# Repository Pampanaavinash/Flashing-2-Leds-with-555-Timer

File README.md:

# Flashing-2-Leds-with-555-Timer

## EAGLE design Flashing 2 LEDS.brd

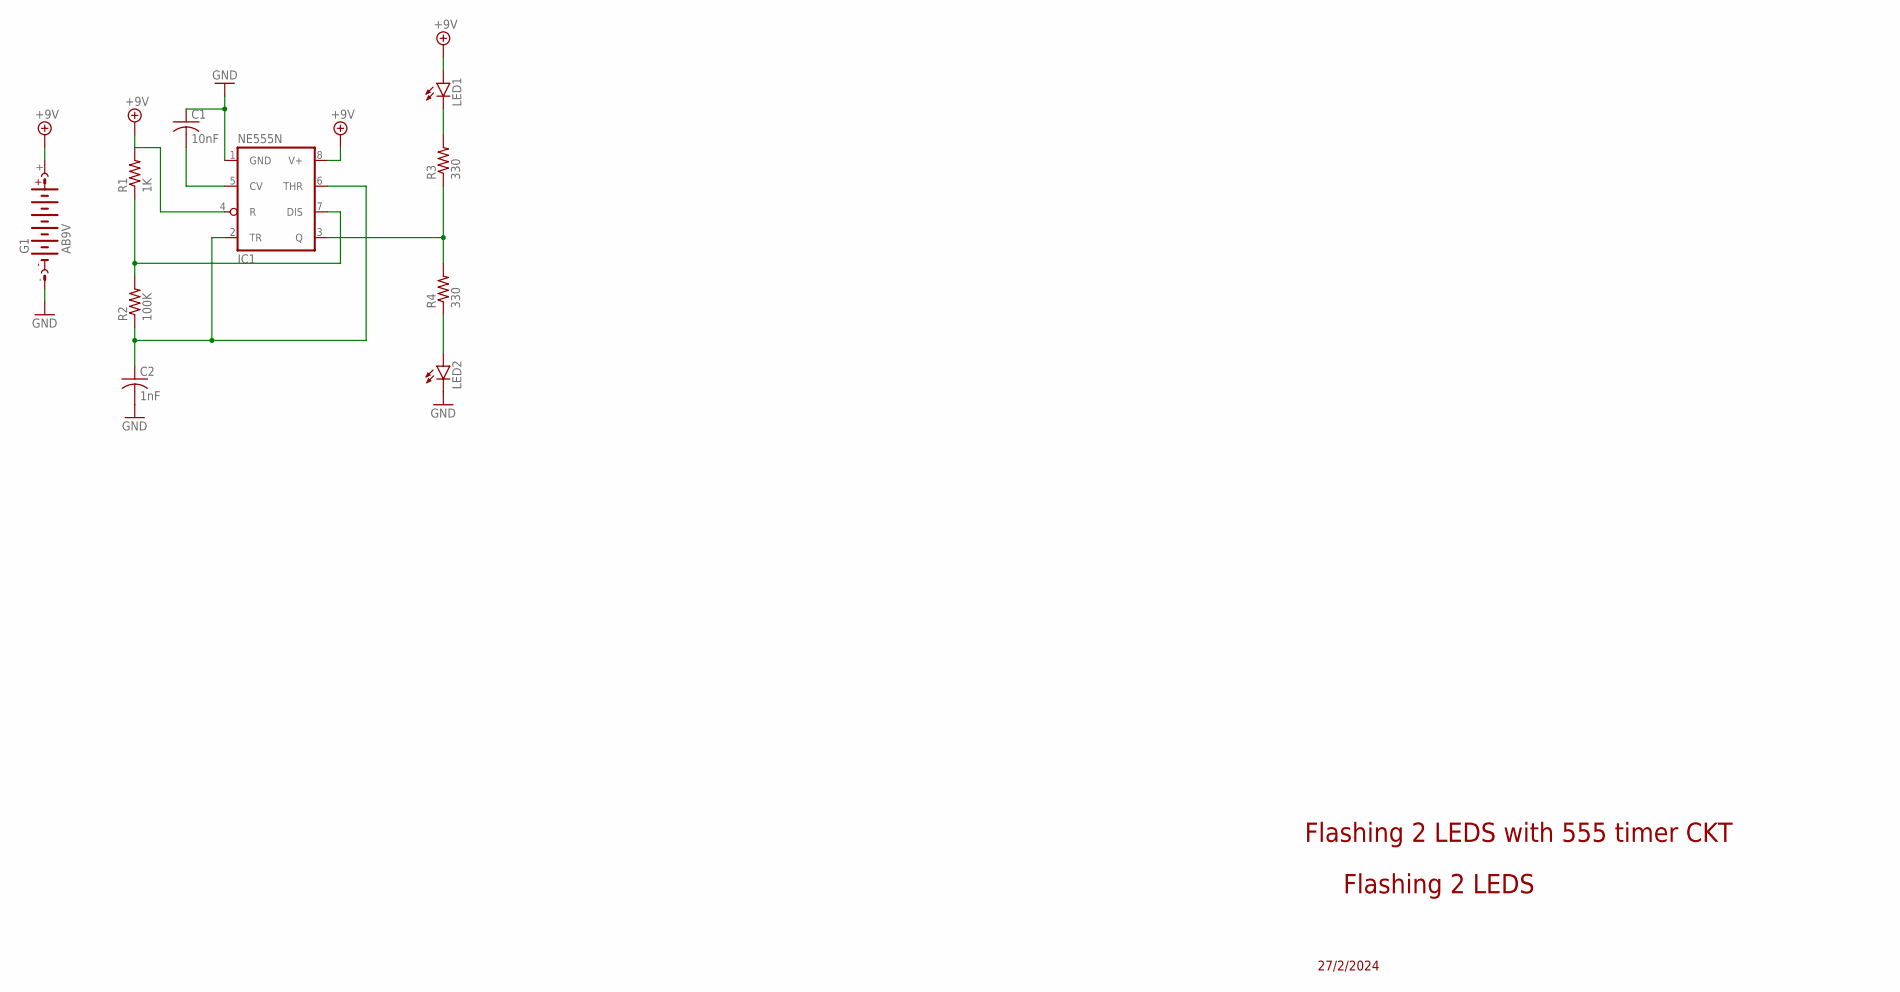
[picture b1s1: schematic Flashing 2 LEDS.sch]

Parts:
C1: 10nF; C1206
C2: 1nF; C1206
G1: AB9V
IC1: NE555N; DIL08
LED1, LED2: LED5MM
R1: 1K; R0603
R2: 100K; R0603
R3, R4: 330; R0603

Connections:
+9V: G1.+, IC1.4 (R), IC1.8 (V+), LED1.A, R1.2
GND: C1.1, C2.2, G1.-, IC1.1 (GND), LED2.K (C)
unnamed: IC1.7 (DIS), R1.1, R2.2
unnamed: C2.1, IC1.2 (TR), IC1.6 (THR), R2.1
unnamed: LED1.K (C), R3.2
unnamed: IC1.3 (Q), R3.1, R4.2
unnamed: LED2.A, R4.1
unnamed: C1.2, IC1.5 (CV)

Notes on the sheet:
Flashing 2 LEDS
27/2/2024
Flashing 2 LEDS with 555 timer CKT

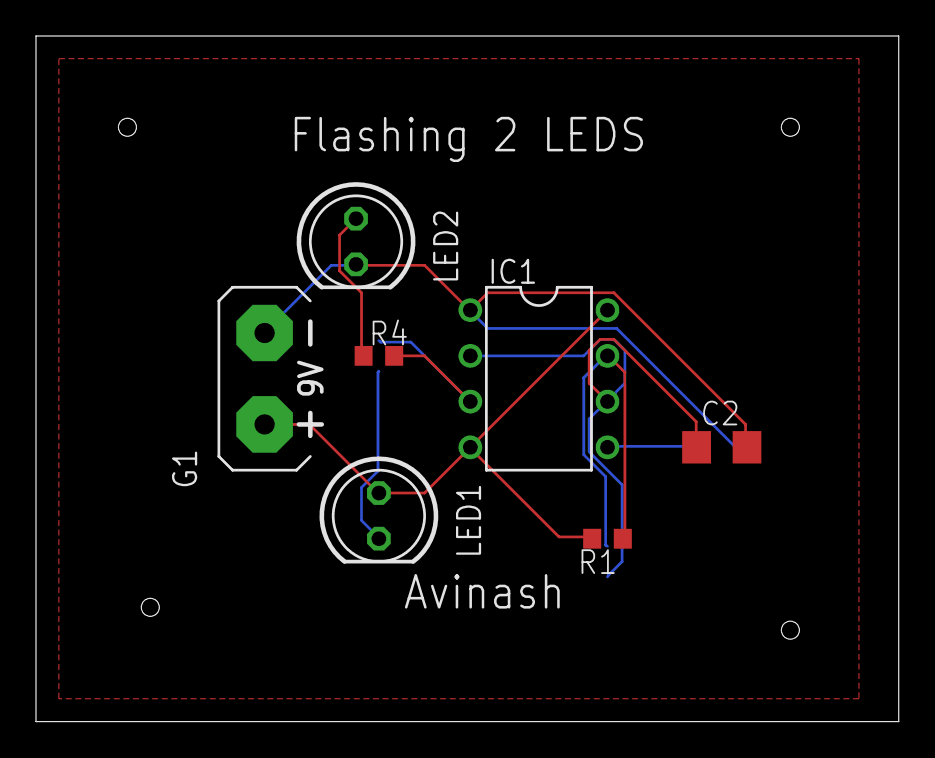
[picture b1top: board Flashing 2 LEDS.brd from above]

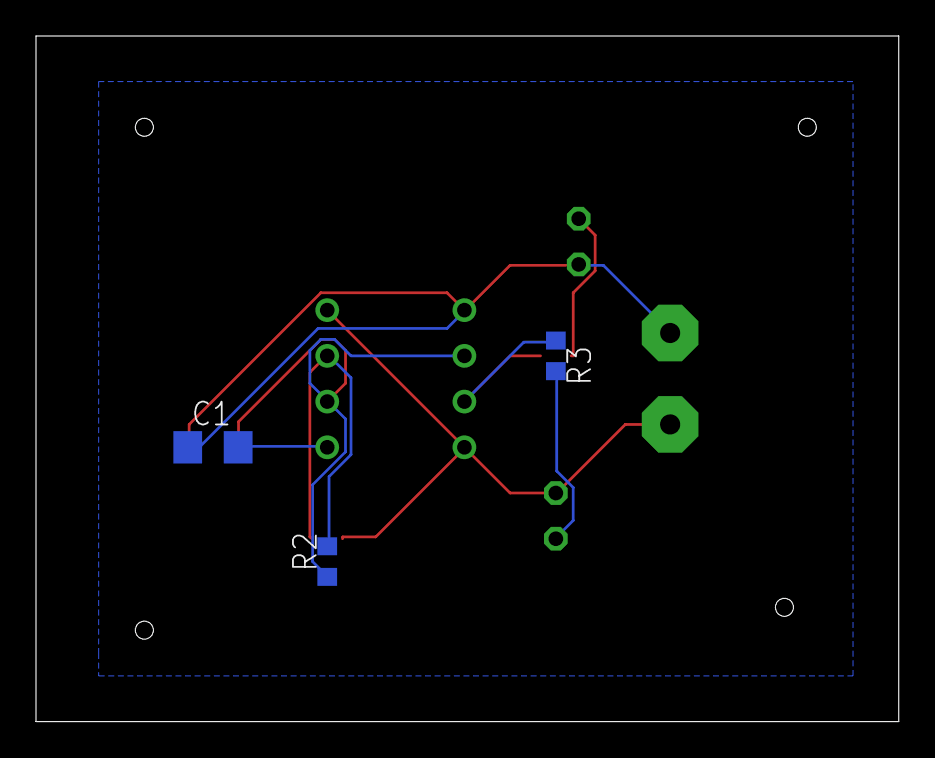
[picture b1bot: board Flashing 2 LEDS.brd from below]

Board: 2 copper layers, 47.9 x 38.1 mm, 10 parts (3 on the bottom side), 8 nets.

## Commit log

2024-03-02 Create Gerber Files
